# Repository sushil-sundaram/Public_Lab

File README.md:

# Public_Lab
This repository will hold all my projects and contributions for Public Lab

Current Projects
- Coquí
  - version - 0.1
  - This is just an intial Layout, any advice or input is appreciated.
  - The size of the PCB is adjusted to a AA battery holder (2.3inches x 1.2inches).
  - Have kept the trace width 24 mils (signals) and 40 mils (power) for ease home manufacturing.

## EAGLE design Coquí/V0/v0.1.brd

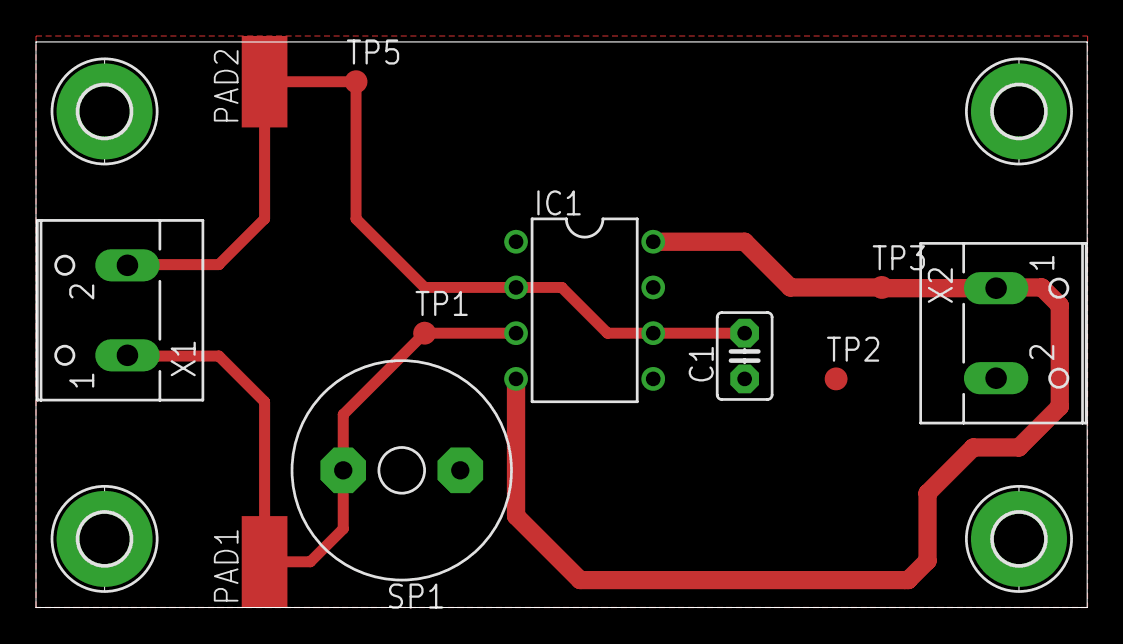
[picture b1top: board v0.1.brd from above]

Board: 2 copper layers, 58.4 x 31.4 mm, 15 parts (0 on the bottom side), 4 nets.

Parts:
C1: C2.5-3
H1, H2, H3, H4: MOUNT-PAD-ROUND2.8; 2,8-PAD
IC1: LM555N; DIL08
PAD1, PAD2: SMD2,54-5,08
SP1: AL60P
TP1, TP2, TP3, TP5: TPB1,27; B1,27
X1, X2: W237-102

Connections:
GND: C1.1, IC1.1, SP1.1, TP2.TP, X2.2
unnamed: C1.2, IC1.2, IC1.6, PAD2.1, TP5.TP, X1.2
unnamed: IC1.3, PAD1.1, SP1.2, TP1.TP, X1.1
VCC: IC1.4, IC1.8, TP3.TP, X2.1

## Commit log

2018-11-20 Added basic PCB design for Coquí project.
    It is a single layer board approximately the size of a AA battery holder (2.3 inches x 1.2 inches )
    - This is an initial version. There may be errors.
    -v0.1
